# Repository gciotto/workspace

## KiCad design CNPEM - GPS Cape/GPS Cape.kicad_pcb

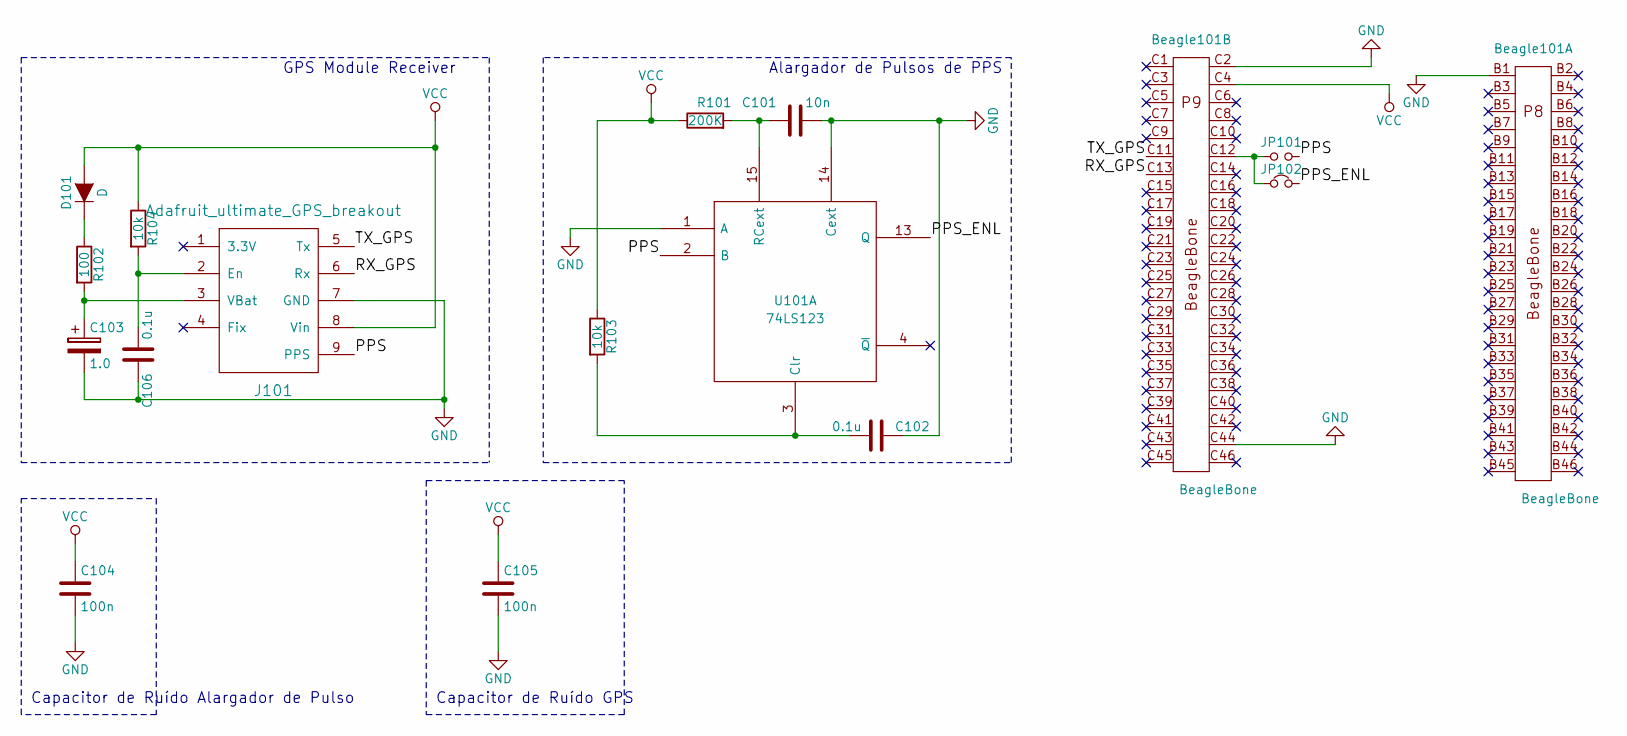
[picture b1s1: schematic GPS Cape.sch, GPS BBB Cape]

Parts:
Beagle101: BeagleBone; BEAGLEBONEBLACK
C101: 10n; C_0805_HandSoldering
C102, C106: 0.1u; C_0805_HandSoldering
C103: 1.0; SuperCap_pads
C104, C105: 100n; C_0805_HandSoldering
D101: D; LED_0805
J101: Adafruit_ultimate_GPS_breakout; Adafruit_Ultimate_GPS_Breakout
JP101: Jumper_NO_Small; Pin_Header_Straight_1x02
JP102: Jumper_NC_Small; Pin_Header_Straight_1x02
R101: 200K; R_0805_HandSoldering
R102: 100; R_0805_HandSoldering
R103, R104: 10k; R_0805_HandSoldering
U101: 74LS123; DIP-16_W7.62mm

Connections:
/PPS: J101.9 (PPS), JP101.2, U101.2 (B)
/PPS_ENL: JP102.2, U101.13 (Q)
/RX_GPS: Beagle101.C13, J101.6 (Rx)
/TX_GPS: Beagle101.C11, J101.5 (Tx)
GND: Beagle101.B1, Beagle101.C2, Beagle101.C44, C101.2, C102.1, C103.2, C104.2, C105.2, C106.1, J101.7 (GND), U101.1 (A), U101.8 (GND), U101.14 (Cext)
unnamed: Beagle101.C12, JP101.1, JP102.1
unnamed: C101.1, R101.2, U101.15 (RCext)
unnamed: C102.2, R103.2, U101.3 (Clr)
unnamed: C103.1, J101.3 (VBat), R102.2
unnamed: C106.2, J101.2 (En), R104.2
unnamed: D101.1 (K), R102.1
VCC: Beagle101.C4, C104.1, C105.1, D101.2 (A), J101.8 (Vin), R101.1, R103.1, R104.1, U101.16 (VCC)

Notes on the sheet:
Alargador de Pulsos de PPS
GPS Module Receiver
Capacitor de Ruído Alargador de Pulso
Capacitor de Ruído GPS

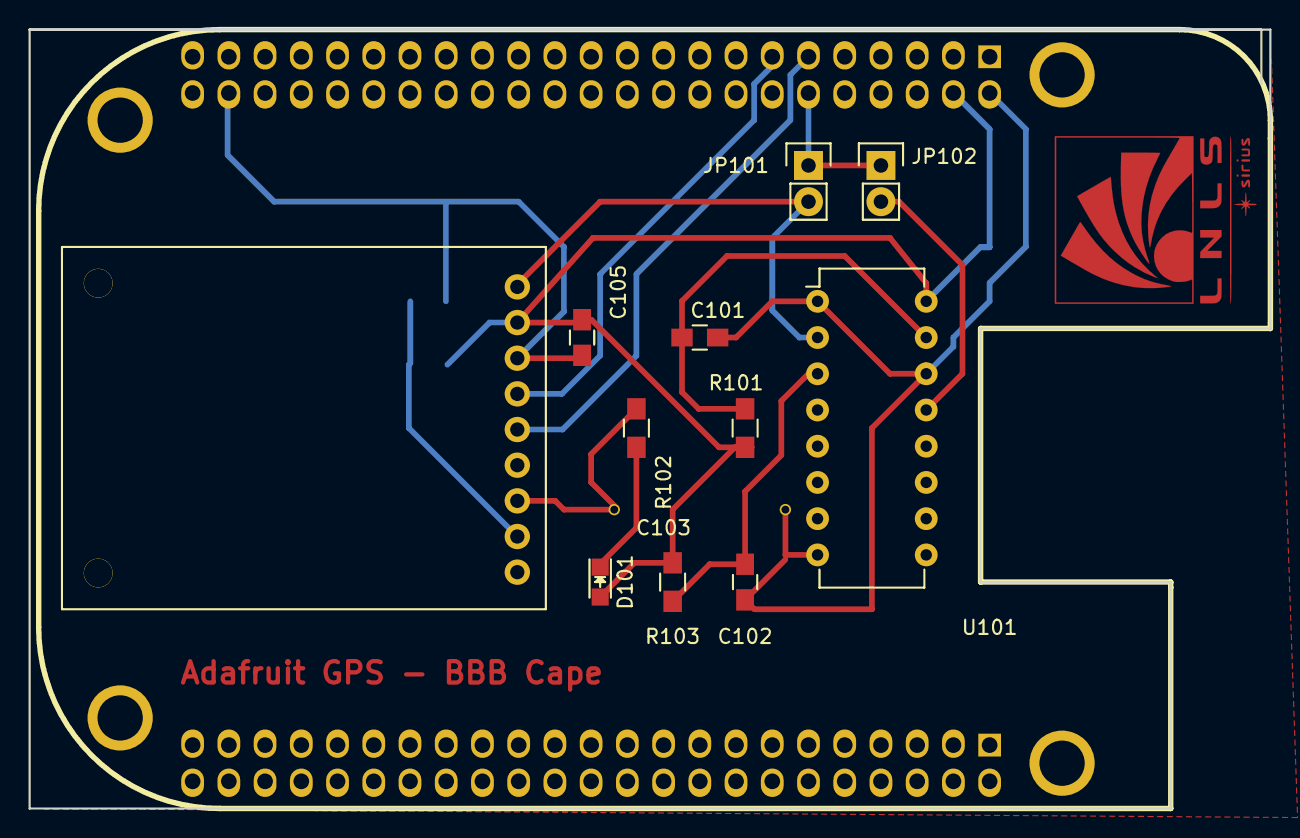
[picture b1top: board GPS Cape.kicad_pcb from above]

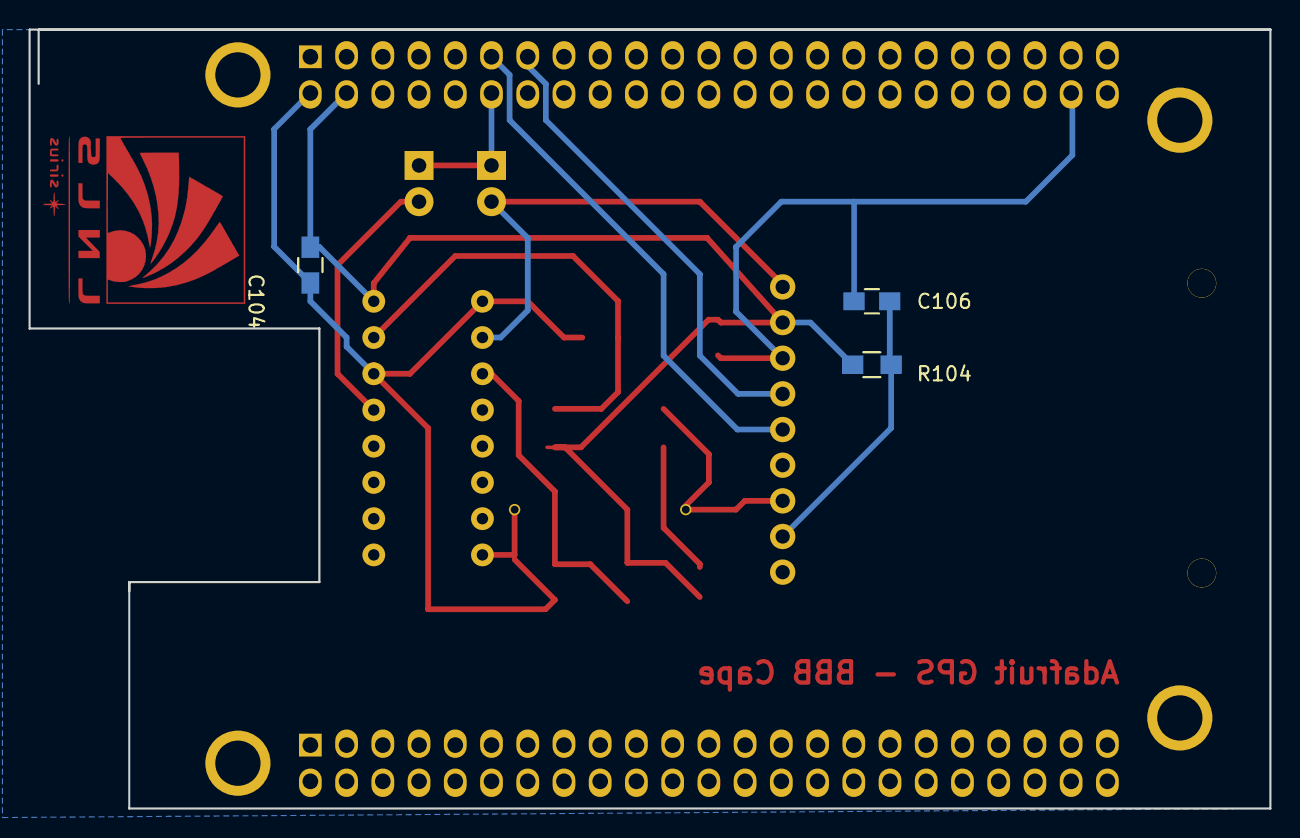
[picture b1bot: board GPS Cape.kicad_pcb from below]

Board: 2 copper layers, 87.0 x 54.6 mm, 16 parts (3 on the bottom side), 12 nets.

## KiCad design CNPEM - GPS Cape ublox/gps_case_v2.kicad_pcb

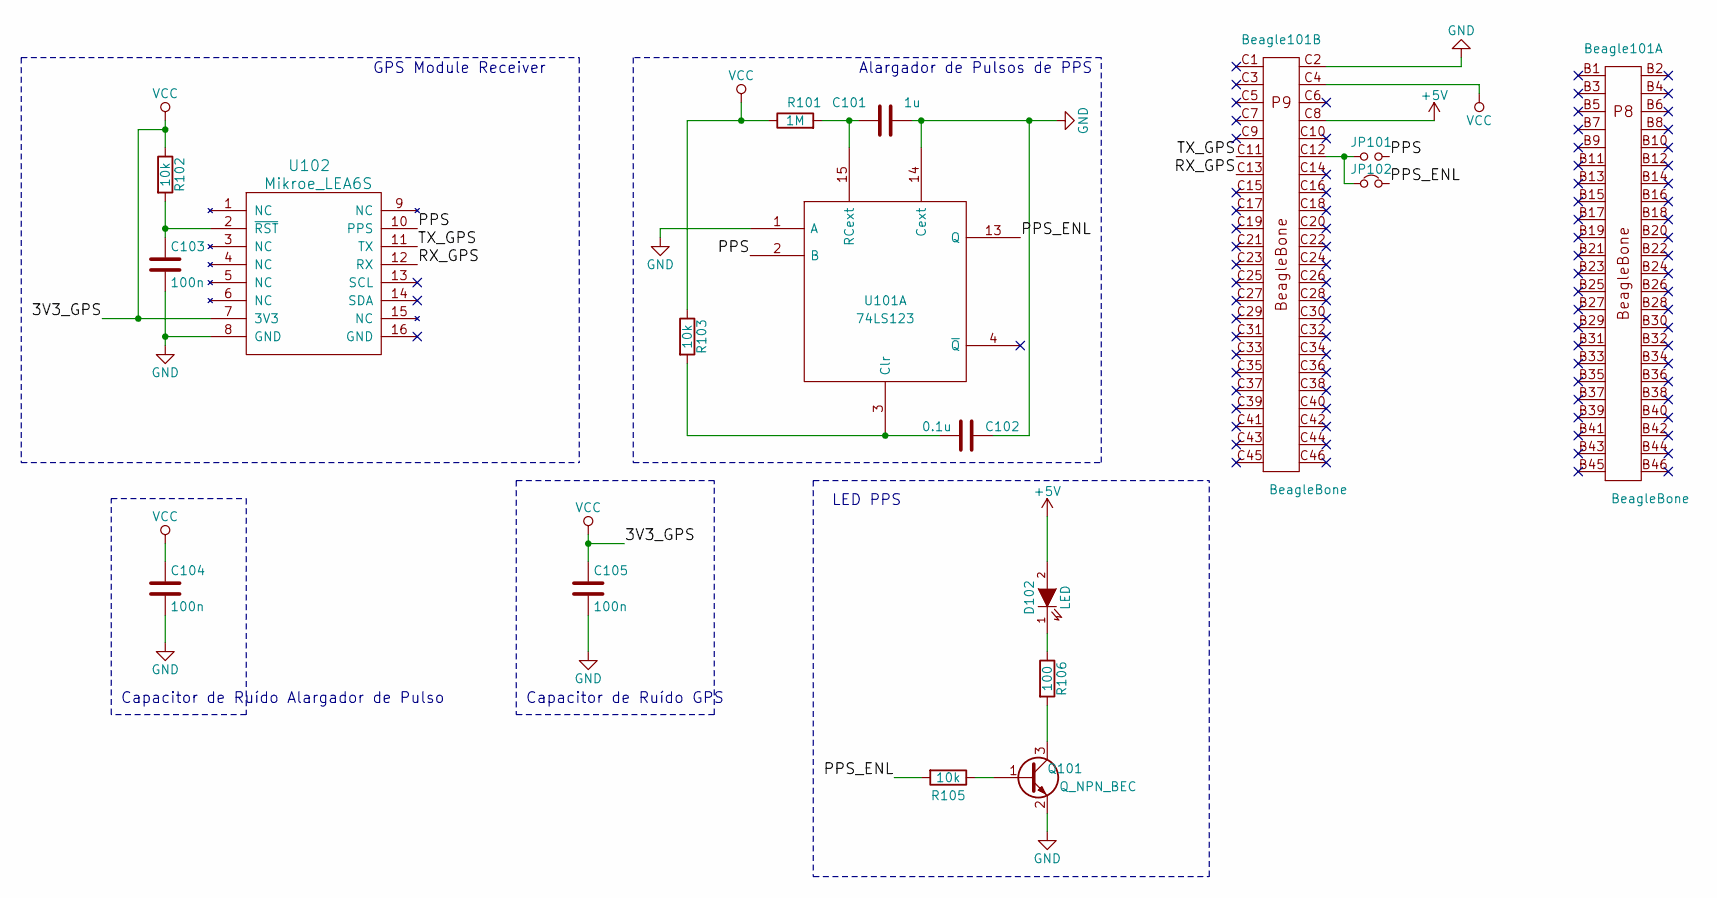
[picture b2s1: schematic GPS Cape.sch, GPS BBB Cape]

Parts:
Beagle101: BeagleBone; BEAGLEBONEBLACK
C101: 1u; C_0805_HandSoldering
C102: 0.1u; C_0805_HandSoldering
C103, C104, C105: 100n; C_0805_HandSoldering
D102: LED; LED_0805
JP101: Jumper_NO_Small; Pin_Header_Straight_1x02
JP102: Jumper_NC_Small; Pin_Header_Straight_1x02
Q101: Q_NPN_BEC; SOT-23_Handsoldering
R101: 1M; R_0805_HandSoldering
R102, R103, R105: 10k; R_0805_HandSoldering
R106: 100; R_0805_HandSoldering
U101: 74LS123; DIP-16_W7.62mm
U102: Mikroe_LEA6S

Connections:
+5V: Beagle101.C8, D102.2 (A)
/PPS: JP101.2, U101.2 (B), U102.10 (PPS)
/PPS_ENL: JP102.2, R105.2, U101.13 (Q)
/RX_GPS: Beagle101.C13, U102.12 (RX)
/TX_GPS: Beagle101.C11, U102.11 (TX)
GND: Beagle101.C2, C101.2, C102.1, C103.2, C104.2, C105.2, Q101.2 (E), U101.1 (A), U101.8 (GND), U101.14 (Cext), U102.8 (GND)
unnamed: Beagle101.C12, JP101.1, JP102.1
unnamed: C101.1, R101.2, U101.15 (RCext)
unnamed: C102.2, R103.2, U101.3 (Clr)
unnamed: C103.1, R102.2, U102.2 (~RST)
unnamed: D102.1 (K), R106.1
unnamed: Q101.1 (B), R105.1
unnamed: Q101.3 (C), R106.2
VCC: Beagle101.C4, C104.1, C105.1, R101.1, R102.1, R103.1, U101.16 (VCC), U102.7 (3V3)

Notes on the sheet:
Alargador de Pulsos de PPS
GPS Module Receiver
Capacitor de Ruído Alargador de Pulso
Capacitor de Ruído GPS
LED PPS

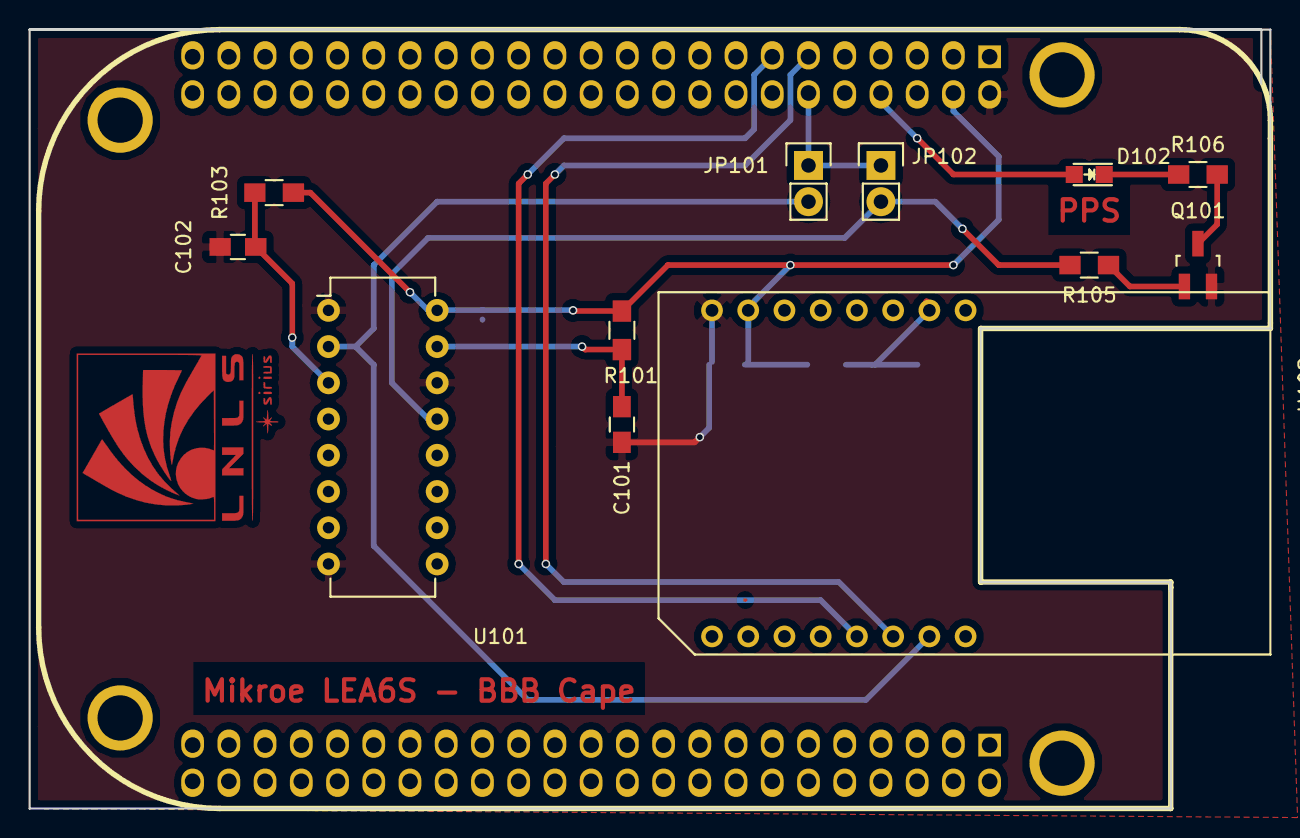
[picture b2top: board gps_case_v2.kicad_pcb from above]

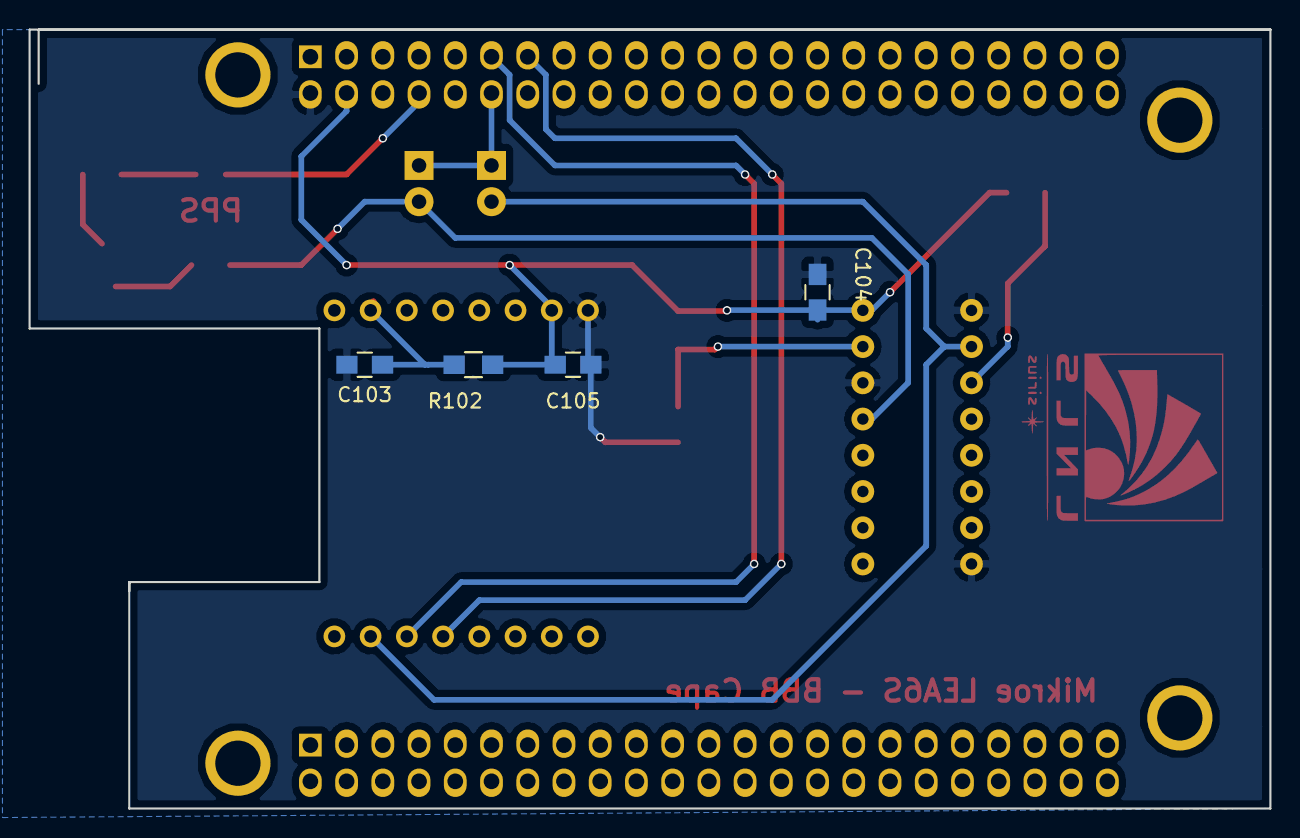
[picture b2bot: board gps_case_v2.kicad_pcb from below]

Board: 2 copper layers, 87.0 x 54.6 mm, 17 parts (4 on the bottom side), 14 nets.

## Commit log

2015-09-27 Inicializacao do repositorio
2015-09-29 Conclusao - EFC1 EA072
2015-09-30 Conclusao - EFC 1 EA072
2015-09-30 EFC 1 EA072 Finalizado
2015-10-01 EA072 EFC1 Finalizado
2015-10-10 CV em portgu"es
2015-10-10 Cover letter AIRBUS
2015-10-10 Segundo paragrafo
2015-10-11 Certificados
2015-10-11 Mudanças CV
2015-10-11 Atualizacao 11/10/2015
2015-10-11 ATUALIZACAO UNICAMP
2015-10-11 ATUALIZACAO UNICAMP EA532
2015-10-11 ATUALIZACAO UNICAMP MC404
2015-10-12 ATUALIZACAO UNICAMP MC302
2015-10-12 ATUALIZACAO UNICAMP MC536
2015-10-12 ATUALIZACAO UNICAMP EA072
2015-10-12 ATUALIZACAO SUPELEC Valorisation dun sujet
2015-10-12 ATUALIZACAO SUPELEC Projet Synthese
2015-10-12 ATUALIZACAO SUPELEC Stage 1A
2015-10-12 ATUALIZACAO SUPELEC Conception Rapport
2015-10-12 ATUALIZACAO SUPELEC Logiciel
2015-10-12 ATUALIZACAO SUPELEC lettre de motivation
2015-10-12 ATUALIZACAO SUPELEC fractales
2015-10-12 ATUALIZACAO SUPELEC CEVV
2015-10-12 ATUALIZACAO SUPELEC FISDA
2015-10-12 ATUALIZACAO SUPELEC Modeles
2015-10-12 ATUALIZACAO SUPELEC Architecture
2015-10-12 Cover letter AIRBUS versao 1
2015-10-12 Cover letter AIRBUS versao final
2015-10-12 pastas renomeadas
2015-10-12 ATUALIZACAO 12/10/2015
2015-10-12 ATUALIZACAO 12/10/2015 - CV
2015-10-13 ATUALIZACAO 12/10/2015 - CV e Cover letter airbus
2015-10-15 atualizaçoes CV e cover letter
2015-10-26 EFC2 e mudancas em cover letter e cv
2015-10-29 EFC2 EA072
2015-10-30 EFC2 - Secao 3
2015-10-31 EFC2 parte 3
2015-11-01 EFC2 Alteracoes
2015-11-03 EA072 EFC2
2015-11-13 EA072 MLP ROBO
2015-11-16 EA072 SCOAL
2015-11-18 Quase terminado
2015-11-19 Pronto
2015-12-04 Atualizacao DEC2015
2016-01-09 Projetos Python
2016-01-13 atualizacao Janeiro 2016
2016-01-16 Atualizacao
2016-01-28 Python V
2016-01-30 Webpages
2016-01-30 Atualizacoes
2016-01-30 teste
2016-01-30 Atualização CV
2016-01-30 web-fonts
2016-01-31 Mudancas site
2016-02-10 Alteracoes Python e Website
2016-02-10 Rodape
2016-02-14 Relatorio CNPEM
2016-02-17 CNPEM - EPICS
2016-02-18 Imagens - CNPEM
2016-02-22 epics
2016-02-23 EPICS Python
2016-02-23 CNPEM
2016-02-24 CNPEM python e c
2016-02-25 CNPEM libbsmp
2016-02-29 Alteracoes CNPEM
2016-03-09 Relatorio
2016-03-10 Relatorio com BEAST
2016-03-11 EA076
2016-03-18 Beagle
2016-04-08 CNPEM Files
2016-04-15 atualizacoes CNPEM
2016-04-19 atualizacoes CV e relatorio
2016-04-25 cnpem relatorio
2016-04-29 historico
2016-05-16 Projeto EA979
2016-05-16 EA076 lab6
2016-05-22 Projeto k-means: tamura.py
2016-05-28 Alteracoes Cliente PROSAC
2016-05-28 Finalizacao da interface
2016-05-29 EA979 T6
2016-05-29 Alteracoes e correcoes
2016-05-30 sub levels kmeans
2016-06-07 Adicao das funcoes de TAMURA
2016-06-13 Project initialization
2016-06-13 Completed version
2016-07-05 updates in the 'Experiencia Profissional' section
2016-07-05 additional support for some boards, commentaries and graphical interfaces changings
2016-07-05 commentaries inserted
2016-07-05 overlay initialization script and commentaries inserted
2016-07-05 graphical interface and final application used to test the new power suppliers
2016-07-05 component library, schematics and pcb files
2016-07-06 unnecessary files deleted
2016-07-06 report, slides and last changes in project
2016-07-06 insert of .project files in repository
2016-07-06 completed project and initialization of repository
2016-07-06 wireshark and log files inserted
2016-07-06 initialization of repository
2016-07-06 introduction section created and some mistakes corrected
2016-07-06 temporary files deleted
2016-07-06 updates in .project
2016-07-06 .gitignore inserted
2016-07-06 .gitignore inserted and project properties updated
2016-07-06 debug files deleted
2016-07-06 debug and release files deleted
2016-07-06 .gitignore added
2016-07-06 debug files removed
2016-07-06 binary file removed
2016-07-06 .gitignore and .project add to the repository
2016-07-06 setting files added to repository
2016-07-06 initialization of repository and commentaries
2016-07-06 .cproject and .project files included
2016-07-06 initialization of repository and .* files inserted
2016-07-06 concatenated file inserted - bulletin supelec
2016-07-06 .pdf and .* files inserted
2016-07-06 .* files inserted
2016-07-10 emits signals when a transmission fails and disconnects Requesters
2016-07-18 schematics and pcb finished
2016-07-19 bbb pins connections put in bottom layer and logo inserted
2016-07-19 .gitignore added and *.pyc removed
2016-07-19 .project refreshed
2016-07-19 .gitignore refreshed
2016-07-21 LNLStudio product initialization
2016-07-21 Makefile added
2016-07-21 *.sh added
2016-07-21 .* included
2016-07-21 version 2 files included
2016-07-21 LED and components revised
2016-07-25 .gitignore updaded with gerber_v2 folder
2016-07-25 .bak file updaded
2016-07-28 OPI interface included
2016-07-29 OPI interfaces and server finished
2016-07-29 old interface deleted
2016-07-29 NTP section finished
2016-07-29 service files and build script finished
2016-07-29 remove old build and dts files
2016-07-29 mikroe gps click cape finished
2016-07-29 .gitignore included
2016-07-29 cape finished
2016-07-29 update in overlay section
2016-07-29 CSS packages included in table
2016-08-01 binary files deleted
2016-08-01 .gitignore correted
2016-08-02 send commands option and bug fixes
2016-08-02 commentaries and two more Node states added
2016-08-02 Additional commentaries and minor changes in log operations
2016-08-03 offset graph included
2016-08-03 dimensions adjusted
2016-08-04 README included
2016-08-04 overlay.sh renamed to overlay_PWM.sh
2016-08-04 node list updated
2016-08-04 unnecessary Board class removed. replaced by BoardsFrame
2016-08-04 .gitignore included and PV prefix update
2016-08-04 README and executable jar included
2016-08-04 netbeans files removed
2016-08-04 .gitignore updated
2016-08-05 README and .gitignore added
2016-08-11 added ca:// to all fields
2016-08-11 LNLStudio feature-based project
2016-08-12 improvements in commentaries and ntplib/gps installation included
2016-08-12 minor bug fixes
2016-08-12 minor changes in order to be compatible with opr22
2016-08-13 /Debug directory added
2016-08-15 _seconds created to specify number of plotting points
2016-08-16 pv server systemd service and init script with symbolic links created
2016-08-16 capemgr.service dependency added
2016-08-16 javadoc generated
2016-08-16 commentary corrected
2016-08-16 commentaries added and 'no boards detected' warning
2016-08-16 .jar updated with latest version
2016-08-16 javadoc generated with Client
2016-08-18 ea4 archive reader feature and pv spcript plugin added
2016-08-19 scripts to start and stop LNLS Archiver appliances
2016-08-19 org.csstudio.platform.libs.epics.ui included
2016-08-19 _used_line uninitialized buf corrected
2016-08-23 buffercontroller.py yields cpu
2016-08-24 archiver systemd files tested
2016-08-24 beast systemd file included
2016-08-24 beast and archiver install section updated
2016-08-24 minor bugs fix
2016-08-24 ln replaced by cp
2016-08-24 +x permission granted
2016-08-24 ntp and ntpdate minor bugs fixes
2016-08-26 exception handling added
2016-08-28 project 1 initialization of repository
2016-08-28 .gitignore files added
2016-08-28 reportable run completed
2016-08-28 make and .so first version
2016-08-28 pintoo finished
2016-08-28 script runs make correctly
2016-08-29 static ins tool executed
2016-08-29 rename folder
2016-08-31 leap alarm included
2016-08-31 logbook and olog features added
2016-09-02 first commit: model and editparts
2016-09-04 first version
2016-09-05 intro and abstract
2016-09-06 section 2
2016-09-06 inscount added
2016-09-08 pintool detailed
2016-09-09 properties, switch and host functionalities added
2016-09-12 almost ready
2016-09-12 first data
2016-09-13 need to review results
2016-09-13 presentation
2016-09-14 to be revised
2016-10-07 changes to apply for master
2016-11-03 project init.
2016-11-03 .* project files
2016-11-03 README => README.md
2016-11-03 Interface test files
2016-11-03 support for HP232
2016-11-03 updates in layout
2016-11-03 new ramps
2016-11-03 .jar with new ramps and cycle curves
2016-11-03 launch options
2016-11-03 Queue() used instead of simple list
2016-11-03 change column headers
2016-11-03 added GERADOR entry
2016-11-03 communication through Stream IOC
2016-11-03 project files
2016-11-03 login page
2016-11-03 mgmt web pages
2016-11-03 cnpem format
2016-11-04 second page according to model
2016-11-11 temporary version report
2016-11-14 first completed version
2016-11-15 project 3 report
2016-11-17 presentation ready
2016-11-17 last version
2016-11-17 motivation section ready
2016-11-17 some new changes
2016-11-18 project reviewed at 17/11
2016-11-18 presentation ready at 16/11
2016-11-18 updated at 18/11
2016-11-20 resumo do relatorio
2016-11-20 ee017 cover
2016-11-24 final
2016-11-28 files to each section
2016-11-29 to be tested
2016-11-29 outline added
2016-11-30 after first test session
2016-11-30 pre test #2
2016-11-30 others sections removed
2016-11-30 2nd test
2016-11-30 3rd test
2016-12-01 final version and annotated version
2016-12-01 final version
2016-12-04 introductions and implementation sections
2016-12-04 report #2 finished
2016-12-04 report #3 finished
2016-12-04 presentation #2 finished
2016-12-04 presentation #3 finished
2016-12-04 results and conclusion missing
2016-12-05 ublox gps receiver photo
2016-12-06 first version of the report
2016-12-07 presentation#4
2016-12-19 removing certificates
